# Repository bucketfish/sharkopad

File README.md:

# sharkopad!

sharkopad is a 6-key macropad with a rotary encoder & an oled screen. it will be your cutest & most favorite desktop buddy :)

features:

- 6 customisable keys
- backlights!!
- a rotary encoder
- a screen
- a yummy shark body

planned features:

- oled screen will show eyes and emotions
- rotary encoder changes layers so you can access more functions
- actually functioning backlights

these firmware changes are hard to test without the actual hardware so i will update it after i assemble it !!

# details

| schematic | pcb |
| ----- | ---- |
|  |  |

it is small and will be assembled with superglue 🙏

# bom

| item | quantity |
| --- | --- |
| cherry mx switches | 6 |
| dsa keycap (ideally: jelly/translucent) | 6 |
| 128x32 oled display | 1 |
| ec11 rotary encoder | 1 |
| seeed xiao rp2040 | 1 |
| 1N4148 diode | 6 |
| SK6812 mini-e led | 6 |
| 1x4 pin header | 1 |
| short f/f 1x4 pin header connector | 1 |
| case (3 printed parts) | 1 |

& superglue...

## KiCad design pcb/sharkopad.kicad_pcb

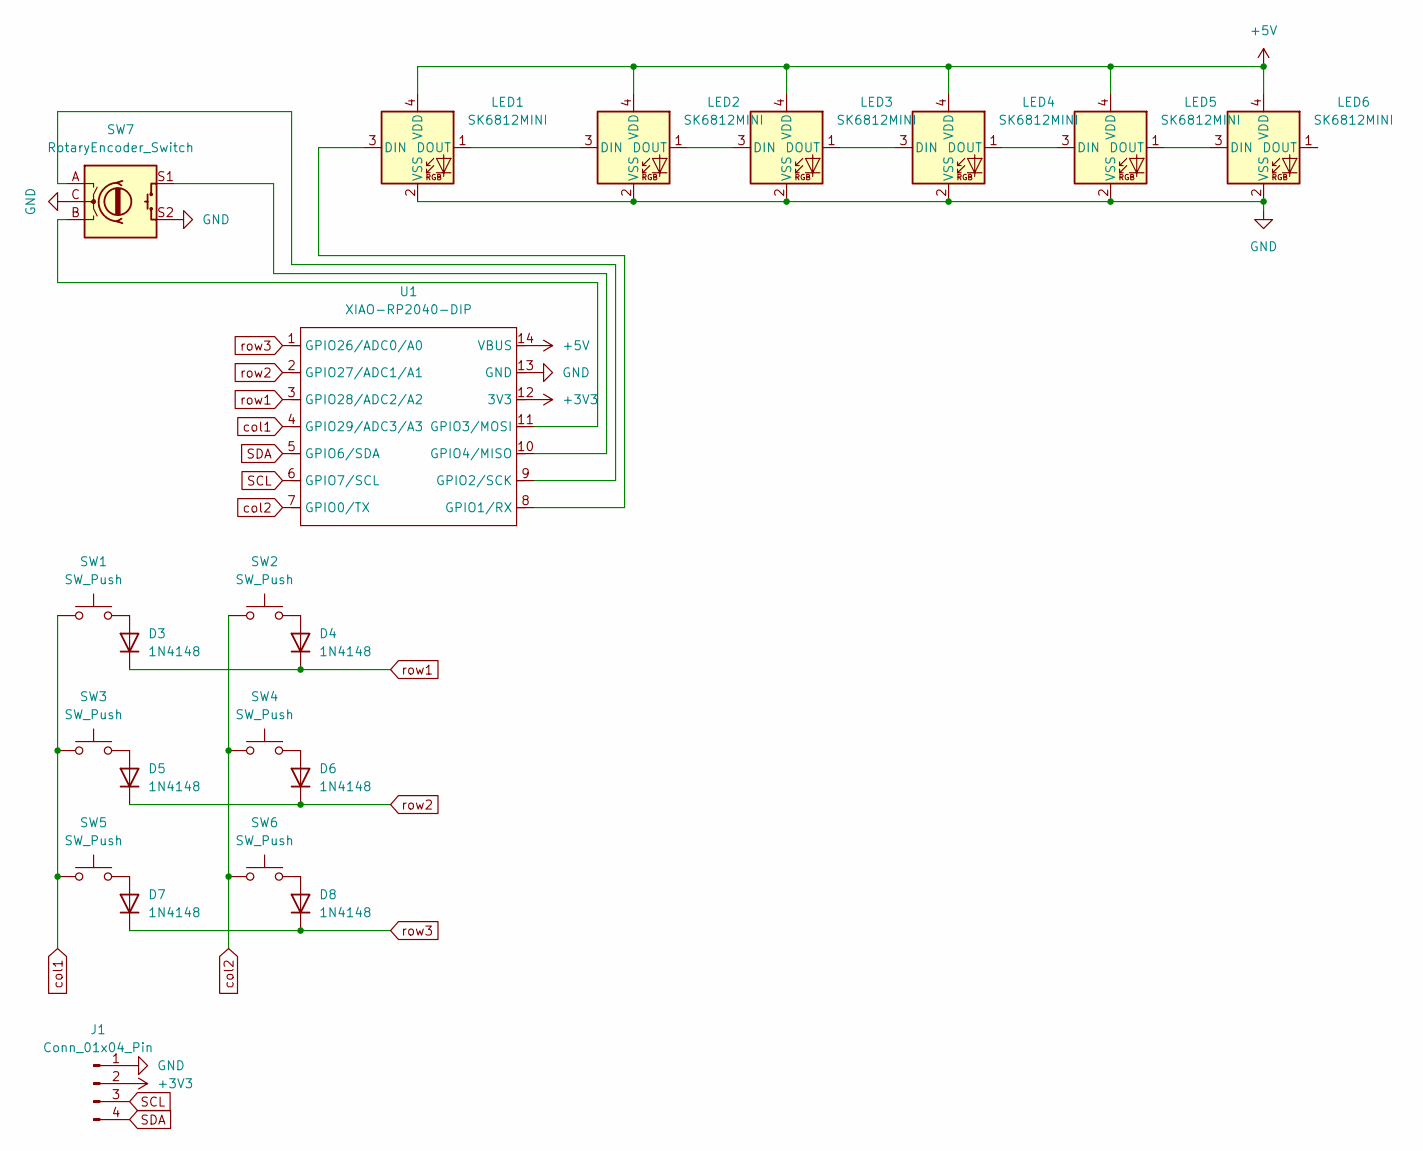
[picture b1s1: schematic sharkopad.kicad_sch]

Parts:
D3, D4, D5, D6, D7, D8: 1N4148; D_DO-35_SOD27_P7.62mm_Horizontal
J1: Conn_01x04_Pin; PinHeader_1x04_P2.54mm_Vertical
LED1, LED2, LED3, LED4, LED5, LED6: SK6812MINI; SK6812-MINI-E_REV
SW1, SW2, SW3, SW4, SW5, SW6: SW_Push; SW_Cherry_MX_1.00u_PCB
SW7: RotaryEncoder_Switch; RotaryEncoder_Alps_EC11E-Switch_Vertical_H20mm
U1: XIAO-RP2040-DIP

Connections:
+3V3: J1.2, U1.12 (3V3)
+5V: LED1.4 (VDD), LED2.4 (VDD), LED3.4 (VDD), LED4.4 (VDD), LED5.4 (VDD), LED6.4 (VDD), U1.14 (VBUS)
GND: J1.1, LED1.2 (VSS), LED2.2 (VSS), LED3.2 (VSS), LED4.2 (VSS), LED5.2 (VSS), LED6.2 (VSS), SW7.C, SW7.S2, U1.13 (GND)
unnamed: D3.2 (A), SW1.2
unnamed: D4.2 (A), SW2.2
unnamed: D5.2 (A), SW3.2
unnamed: D6.2 (A), SW4.2
unnamed: D7.2 (A), SW5.2
unnamed: D8.2 (A), SW6.2
unnamed: LED1.3 (DIN), U1.8 (GPIO1/RX)
unnamed: LED1.1 (DOUT), LED2.3 (DIN)
unnamed: LED2.1 (DOUT), LED3.3 (DIN)
unnamed: LED3.1 (DOUT), LED4.3 (DIN)
unnamed: LED4.1 (DOUT), LED5.3 (DIN)
unnamed: LED5.1 (DOUT), LED6.3 (DIN)
unnamed: SW7.A, U1.9 (GPIO2/SCK)
unnamed: SW7.B, U1.11 (GPIO3/MOSI)
unnamed: SW7.S1, U1.10 (GPIO4/MISO)
SCL: J1.3, U1.6 (GPIO7/SCL)
SDA: J1.4, U1.5 (GPIO6/SDA)
col1: SW1.1, SW3.1, SW5.1, U1.4 (GPIO29/ADC3/A3)
col2: SW2.1, SW4.1, SW6.1, U1.7 (GPIO0/TX)
row1: D3.1 (K), D4.1 (K), U1.3 (GPIO28/ADC2/A2)
row2: D5.1 (K), D6.1 (K), U1.2 (GPIO27/ADC1/A1)
row3: D7.1 (K), D8.1 (K), U1.1 (GPIO26/ADC0/A0)

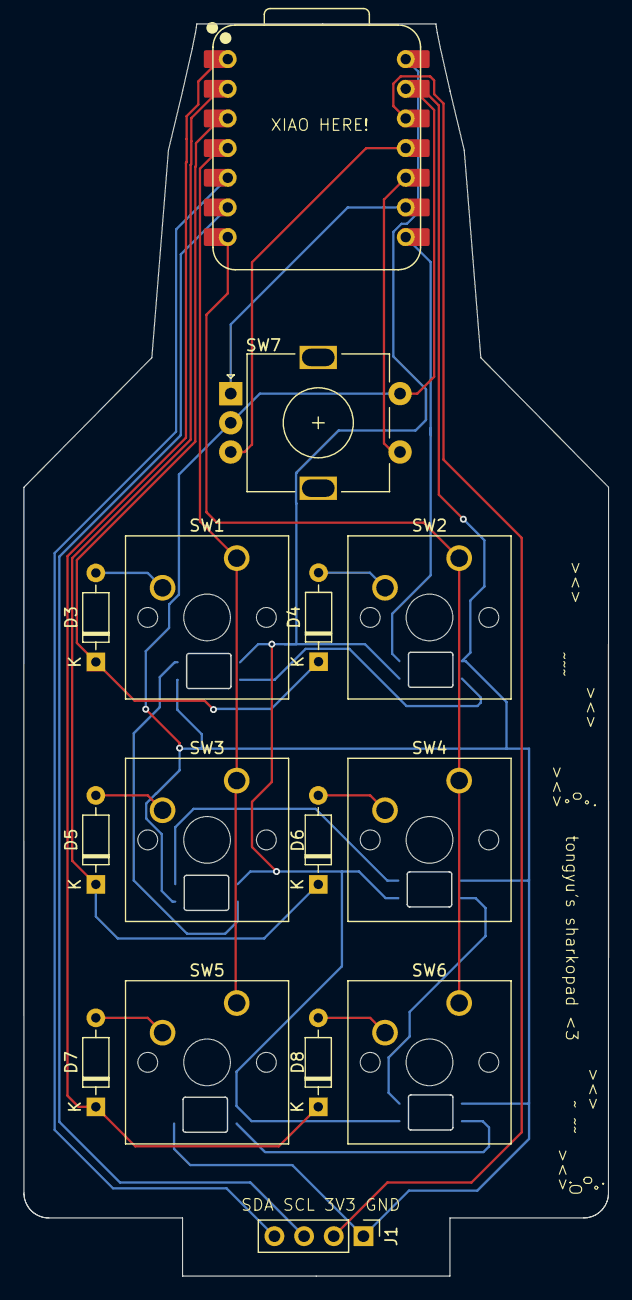
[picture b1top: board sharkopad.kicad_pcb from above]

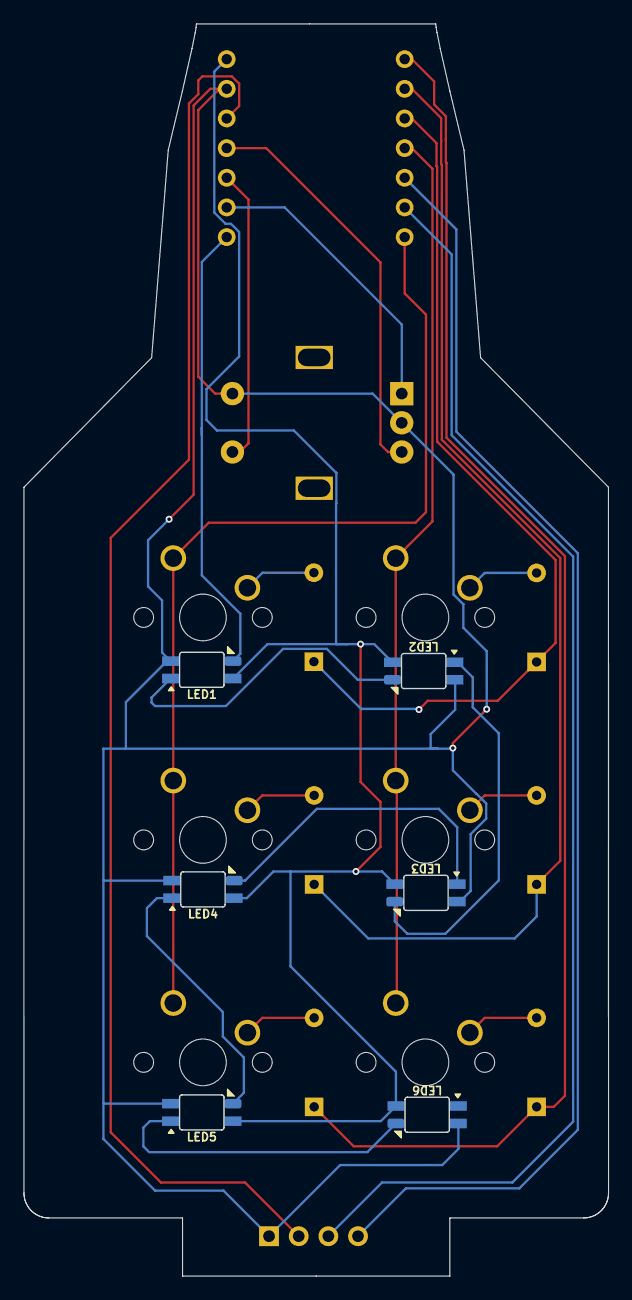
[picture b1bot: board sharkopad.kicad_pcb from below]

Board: 2 copper layers, 50.0 x 107.2 mm, 21 parts (6 on the bottom side), 25 nets.

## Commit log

2025-07-29 sharkopad files
